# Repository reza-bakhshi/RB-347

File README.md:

<div align="center">

# RB-347

**A compact, multi-protocol USB interface module based on the CH347F**

</div>

RB-347 is a small USB interface and debugging module built around the WCH
CH347F. It provides several commonly used digital interfaces from a single
USB-C connection, making it useful for embedded development, board bring-up,
programming, debugging, protocol testing, and laboratory work.

Unlike a basic single-function USB adapter, the CH347F can expose multiple
hardware interfaces through one device. This allows compatible protocols to be
used at the same time, subject to the CH347F operating mode, pin multiplexing,
driver, and host-software support.

## PCB gallery

<table>
  <tr>
    <th width="50%">Top</th>
    <th width="50%">Bottom</th>
  </tr>
  <tr>
    <td></td>
    <td></td>
  </tr>
</table>

## Supported interfaces

- Two UART channels with hardware flow-control and modem-control signals
- SPI with clock, MOSI, MISO, and chip-select signals
- I²C with onboard SDA and SCL pull-up resistors
- JTAG for programming and debugging compatible targets
- SWD signals shared with the JTAG pins
- Multiplexed GPIO signals for general-purpose control

Some CH347F pins have more than one function. Interfaces that use the same
multiplexed pins cannot be enabled independently at the same time; select a
compatible operating mode for the required combination.

## Hardware features

- WCH CH347F USB high-speed multi-interface bridge
- USB-C connector for host connection and board power
- USB data-line ESD protection
- USB-C configuration resistors
- 8 MHz external crystal
- Separate regulated 3.3 V and 1.8 V rails
- Slide switch for selecting the I/O voltage between 3.3 V and 1.8 V
- DIP switch for enabling or disabling the onboard I²C pull-up resistors
- LED indicator for the I²C pull-up resistor status
- Power indicator LED
- Three 10-pin, 2.54 mm interface headers
- Onboard I²C pull-up resistors
- Compact PCB designed in KiCad

## Exposed signals

The headers provide access to the CH347F interface and control signals,
including:

| Group | Signals |
| --- | --- |
| UART 0 | `TXD0`, `RXD0`, `CTS0/GPIO0`, `RTS0/GPIO1`, `DTR0/TNOW0/GPIO2` |
| UART 1 / I²C | `TXD1`, `RXD1`, `CTS1/SCL`, `RTS1/SDA`, `DTR1/TNOW1/SCS1` |
| SPI | `SCK`, `MOSI`, `MISO`, `SCS0`, `SCS1` |
| JTAG / SWD / GPIO | `TCK/SWDCLK/GPIO4`, `TMS/SWDIO/GPIO7`, `TDI/GPIO6`, `TDO/GPIO5`, `TRST/GPIO3`, `ACT/SRST` |
| Control and power | `RST`, `VIO`, `VBUS`, `3.3V`, and `GND` |

## Configuration switches

### I/O voltage

The slide switch selects the voltage used by the CH347F interface pins:

- **3.3 V** for targets that use 3.3 V logic
- **1.8 V** for targets that use 1.8 V logic

Set the switch to match the target's logic voltage before connecting any signal
pins. Do not change the I/O voltage while the module is connected to an active
target.

### I²C pull-ups

The DIP switch enables or disables the onboard pull-up resistors on the I²C
`SDA` and `SCL` lines. Enable them when the bus requires pull-ups and suitable
pull-ups are not already present. Disable them when the target board provides
its own pull-ups or when these pins are used for another multiplexed function.
The I²C indicator LED turns on when the onboard pull-up resistors are enabled
and turns off when they are disabled, providing a clear visual status.

> [!CAUTION]
> Verify the target voltage and the selected I/O configuration before connecting
> RB-347 to another board. Never assume that a target is 5 V tolerant, and do
> not short a target's power rail to USB `VBUS` or another driven supply.

## Typical applications

- USB-to-UART console and serial communication
- SPI and I²C device evaluation
- Flash-memory programming
- JTAG or SWD target programming and debugging
- Automated hardware testing and production fixtures
- Protocol bridging and embedded-system development

---

<div align="center">
  <sub>Built as a compact, versatile interface for embedded development and debugging.</sub>
</div>

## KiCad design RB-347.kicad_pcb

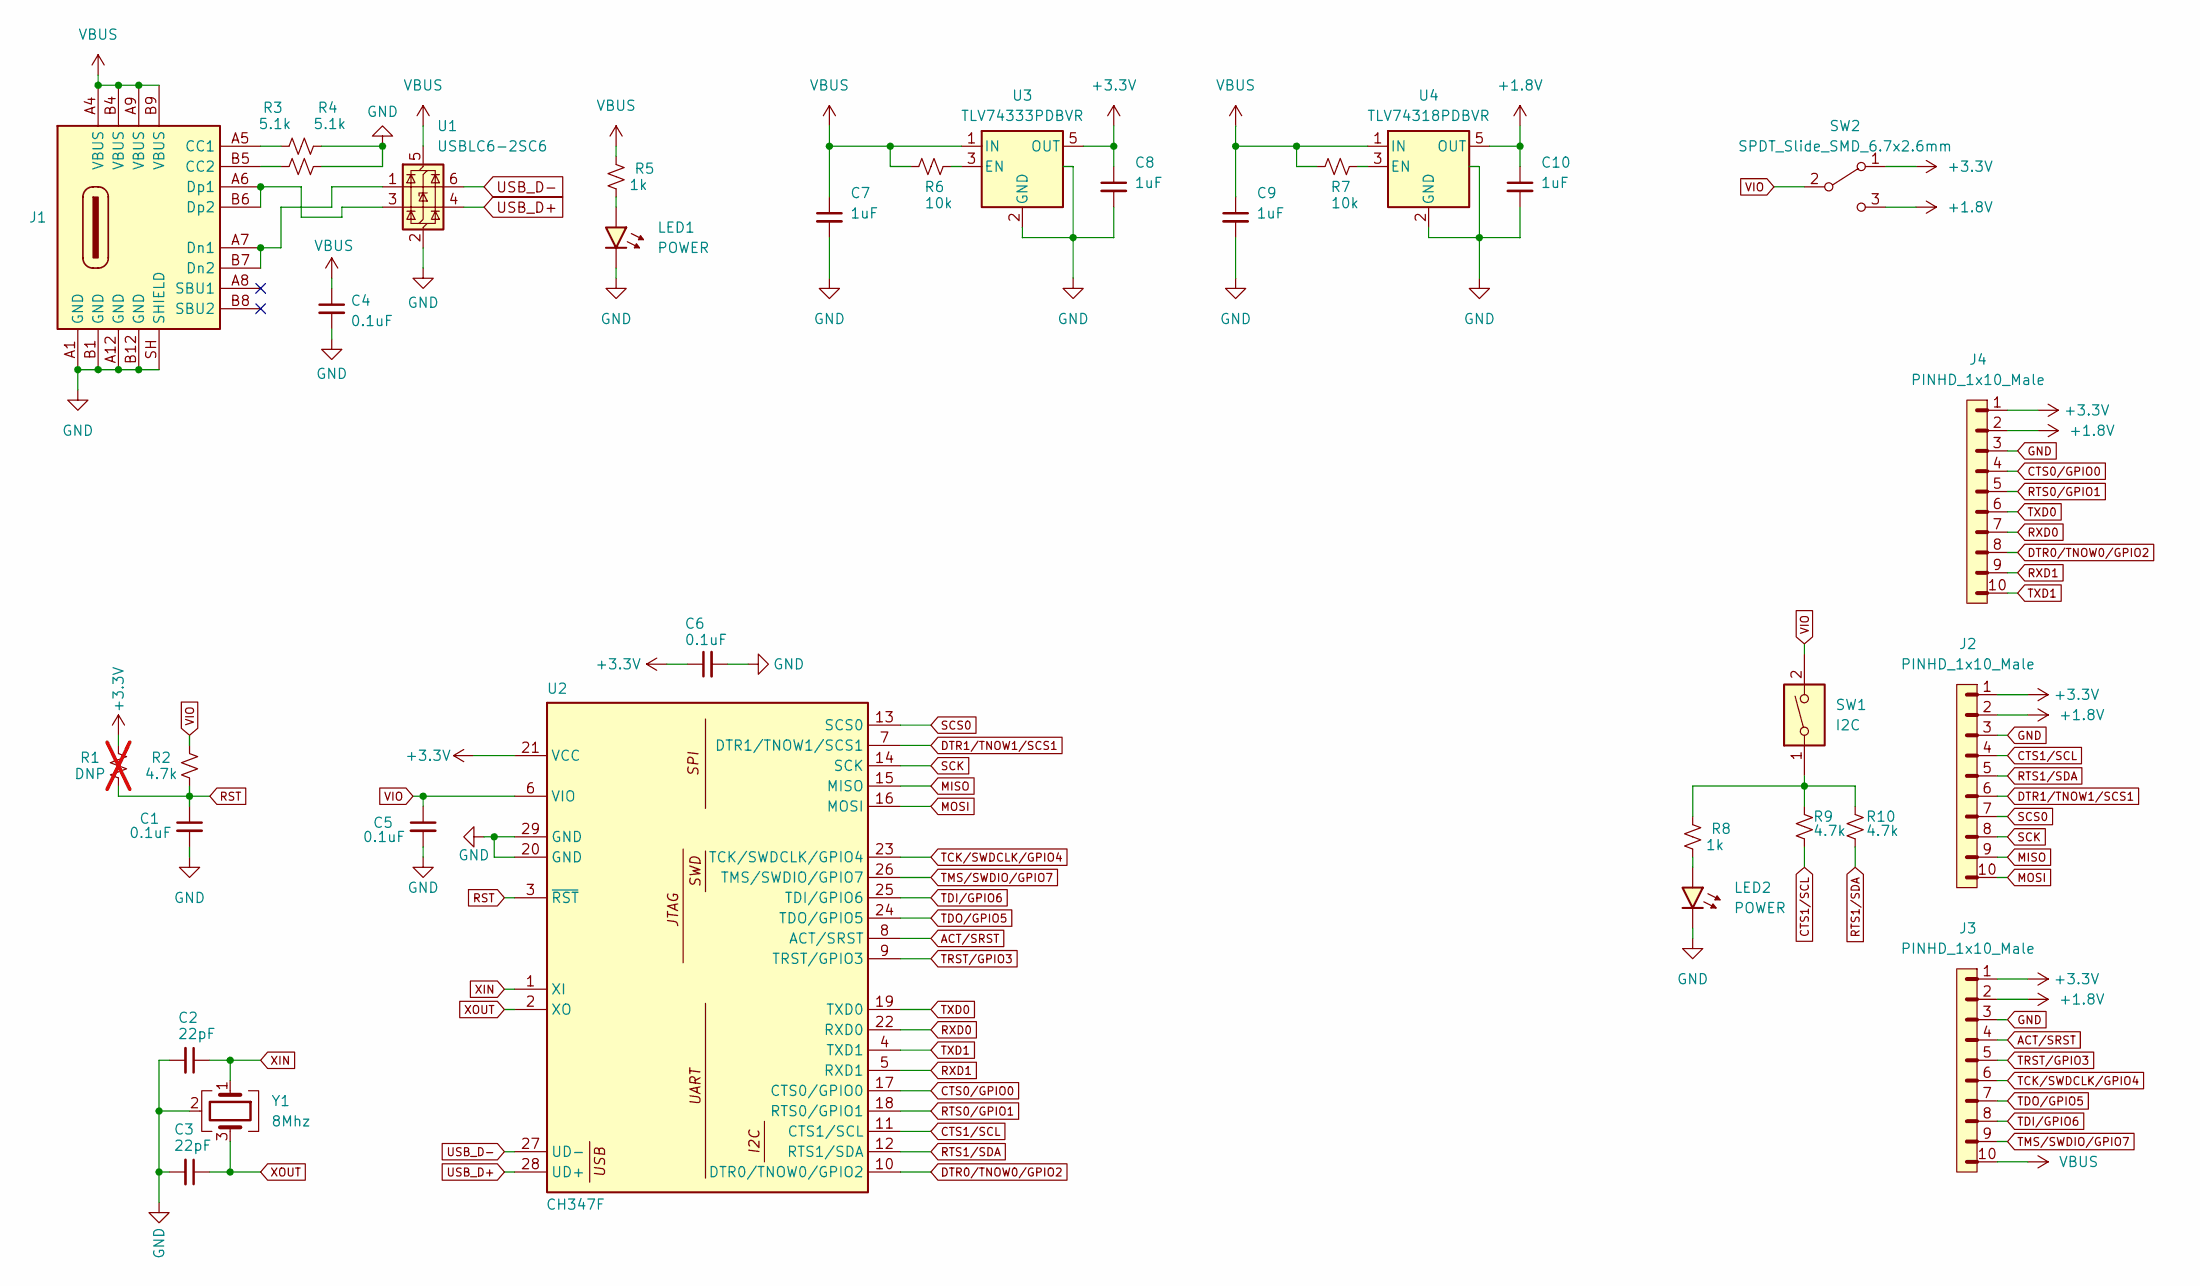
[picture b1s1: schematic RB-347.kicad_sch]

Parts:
C1, C4, C5, C6: 0.1uF; C_0402_1005Metric; Voltage 25V
C2, C3: 22pF; C_0402_1005Metric
C7, C8, C9, C10: 1uF; C_0402_1005Metric; Voltage 25V
J1: Conn_USB_C_Socket; USB_C_Receptacle_GCT_USB4105-xx-A_16P_TopMnt_Horizontal
J2, J3, J4: PINHD_1x10_Male; PinHeader_1x10_P2.54mm_Horizontal
LED1, LED2: POWER; LED_0402_1005Metric_Red
R1: DNP; R_0402_1005Metric; not fitted
R2, R9, R10: 4.7k; R_0402_1005Metric
R3, R4: 5.1k; R_0402_1005Metric
R5, R8: 1k; R_0402_1005Metric
R6, R7: 10k; R_0402_1005Metric
SW1: I2C; SW_DIP_SPSTx01_Slide_6.7x4.1mm_W6.73mm_P2.54mm_LowProfile_J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
SW2: SPDT_Slide_SMD_6.7x2.6mm; Slide_SPST_SMD_6.7x2.6mm; Mrg Part# CUS-12B
U1: USBLC6-2SC6; SOT-23-6
U2: CH347F; QFN-28-1EP_4x4mm_P0.4mm_EP2.6x2.6mm
U3: TLV74333PDBVR; SOT-23-5
U4: TLV74318PDBVR; SOT-23-5
Y1: 8Mhz; Crystal_SMD_3225-4Pin_3.2x2.5mm

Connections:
+1.8V: C10.1, J2.2, J3.2, J4.2, SW2.3 (C), U4.5 (OUT)
+3.3V: C6.1, C8.1, J2.1, J3.1, J4.1, R1.1, SW2.1 (A), U2.21 (VCC), U3.5 (OUT)
ACT/SRST: J3.4, U2.8 (ACT/SRST)
CTS0/GPIO0: J4.4, U2.17 (CTS0/GPIO0)
CTS1/SCL: J2.4, R9.2, U2.11 (CTS1/SCL)
DTR0/TNOW0/GPIO2: J4.8, U2.10 (DTR0/TNOW0/GPIO2)
DTR1/TNOW1/SCS1: J2.6, U2.7 (DTR1/TNOW1/SCS1)
GND: C1.2, C2.2, C3.2, C4.2, C5.2, C6.2, C7.2, C8.2, C9.2, C10.2, J1.A1 (GND), J1.A12 (GND), J1.B1 (GND), J1.B12 (GND), J1.SH (SHIELD), J2.3, J3.3, J4.3, LED1.1 (K), LED2.1 (K), R3.2, R4.2, U1.2 (GND), U2.20 (GND), U2.29 (GND), U3.2 (GND), U3.4 (GND), U4.2 (GND), U4.4 (GND), Y1.2 (G), Y1.4 (G)
MISO: J2.9, U2.15 (MISO)
MOSI: J2.10, U2.16 (MOSI)
unnamed: J1.A5 (CC1), R3.1
unnamed: J1.B5 (CC2), R4.1
unnamed: J1.A7 (Dn1), J1.B7 (Dn2), U1.1 (I/O1)
unnamed: J1.A6 (Dp1), J1.B6 (Dp2), U1.3 (I/O2)
unnamed: LED1.2 (A), R5.1
unnamed: LED2.2 (A), R8.1
unnamed: R8.2, R9.1, R10.1, SW1.1
unnamed: R6.1, U3.3 (EN)
unnamed: R7.1, U4.3 (EN)
RST: C1.1, R1.2, R2.2, U2.3 (~RST)
RTS0/GPIO1: J4.5, U2.18 (RTS0/GPIO1)
RTS1/SDA: J2.5, R10.2, U2.12 (RTS1/SDA)
RXD0: J4.7, U2.22 (RXD0)
RXD1: J4.9, U2.5 (RXD1)
SCK: J2.8, U2.14 (SCK)
SCS0: J2.7, U2.13 (SCS0)
TCK/SWDCLK/GPIO4: J3.6, U2.23 (TCK/SWDCLK/GPIO4)
TDI/GPIO6: J3.8, U2.25 (TDI/GPIO6)
TDO/GPIO5: J3.7, U2.24 (TDO/GPIO5)
TMS/SWDIO/GPIO7: J3.9, U2.26 (TMS/SWDIO/GPIO7)
TRST/GPIO3: J3.5, U2.9 (TRST/GPIO3)
TXD0: J4.6, U2.19 (TXD0)
TXD1: J4.10, U2.4 (TXD1)
USB_D+: U1.4 (I/O2), U2.28 (UD+)
USB_D-: U1.6 (I/O1), U2.27 (UD-)
VBUS: C4.1, C7.1, C9.1, J1.A4 (VBUS), J1.A9 (VBUS), J1.B4 (VBUS), J1.B9 (VBUS), J3.10, R5.2, R6.2, R7.2, U1.5 (VBUS), U3.1 (IN), U4.1 (IN)
VIO: C5.1, R2.1, SW1.2, SW2.2, U2.6 (VIO)
XIN: C2.1, U2.1 (XI), Y1.1
XOUT: C3.1, U2.2 (XO), Y1.3

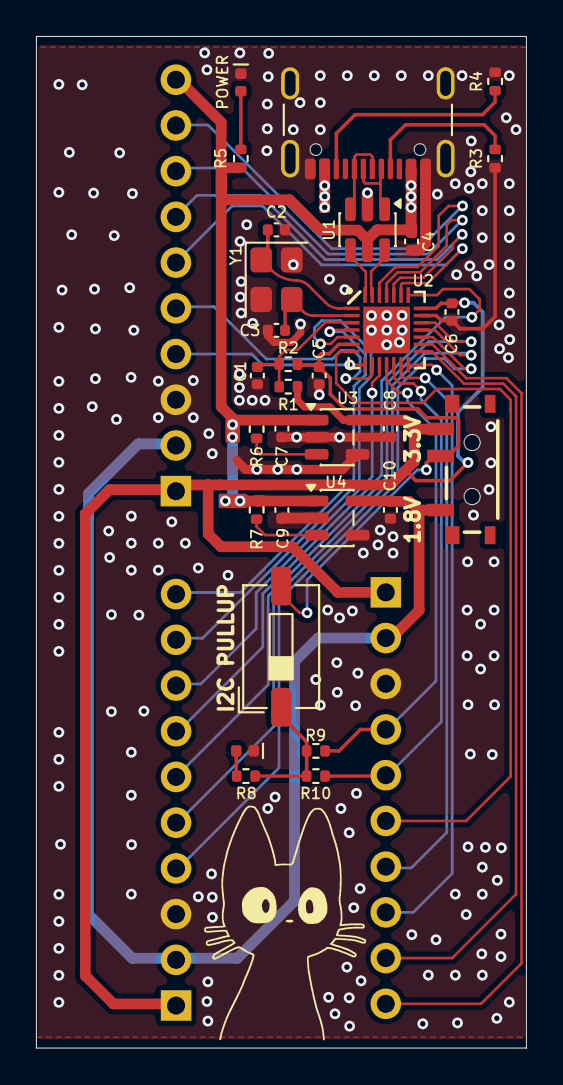
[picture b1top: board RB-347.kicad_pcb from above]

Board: 2 copper layers, 27.2 x 56.2 mm, 33 parts (0 on the bottom side), 39 nets.
